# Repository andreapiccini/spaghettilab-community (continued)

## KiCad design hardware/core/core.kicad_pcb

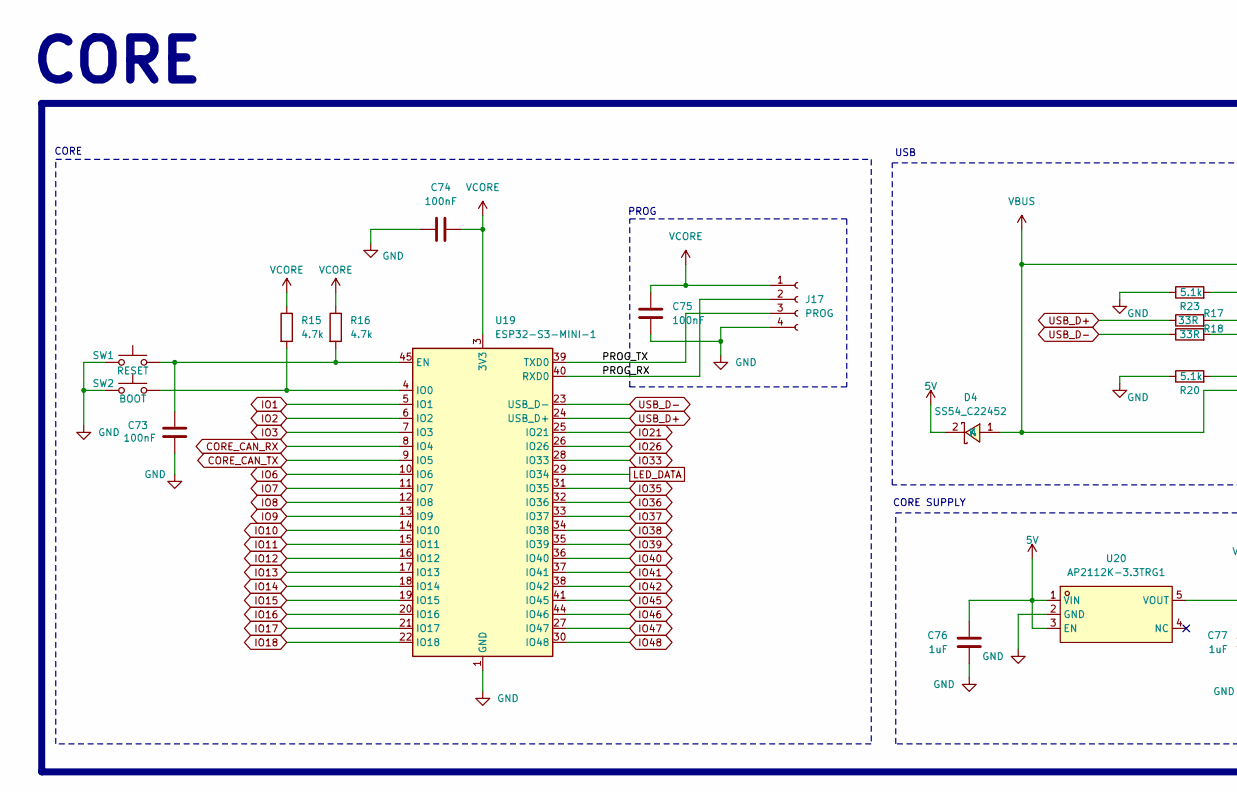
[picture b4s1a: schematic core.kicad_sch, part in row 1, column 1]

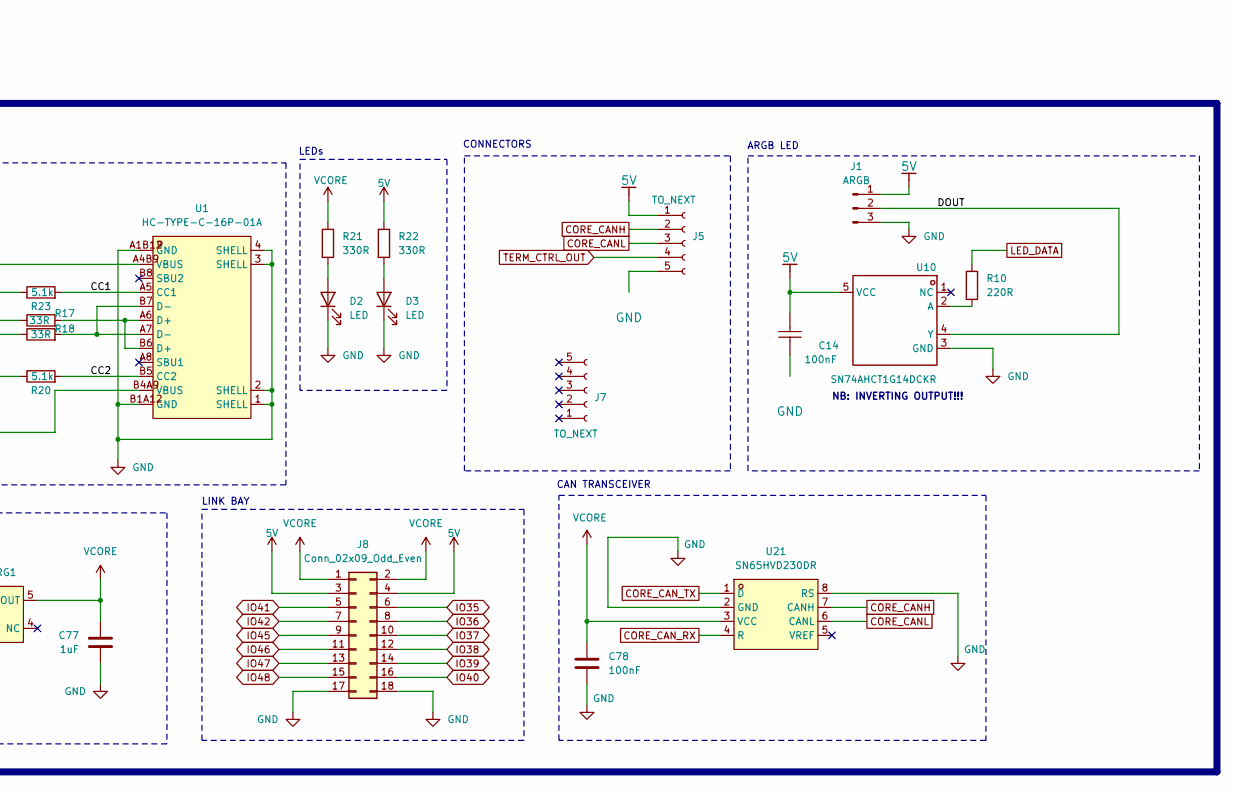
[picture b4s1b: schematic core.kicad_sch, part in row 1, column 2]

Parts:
C14, C73, C74, C75: 100nF; C0603; LCSC Part C1591
C76, C77: 1uF; C0603; LCSC Part C128624
C78: 100nF; C0603; MPN CL05B104KA5NNNC; LCSC Part C1591
D2, D3: LED; LED0603-RD; LCSC Part C19273150
D4: SS54_C22452; SMA_L4.4-W2.8-LS5.4-R-RD; MPN SS54; LCSC Part C22452
J1: ARGB; PinHeader_1x03_P2.54mm_Vertical
J5, J7: TO_NEXT; PinSocket_1x05_P2.54mm_Horizontal
J8: Conn_02x09_Odd_Even; PinSocket_2x09_P2.54mm_Horizontal
J17: PROG; PinSocket_1x04_P2.54mm_Vertical
R10: 220R; R0603; LCSC Part C22962
R15, R16: 4.7k; R0603; LCSC Part C99782
R17, R18: 33R; R0603; LCSC Part C2909394
R20, R23: 5.1k; R0603; LCSC Part C2907044
R21, R22: 330R; R0603; LCSC Part C105881
SW1: RESET; SW-SMD_4P-L5.1-W5.1-P3.70-LS6.5-TL_H1.5; LCSC Part C318884
SW2: BOOT; SW-SMD_4P-L5.1-W5.1-P3.70-LS6.5-TL_H1.5; LCSC Part C318884
U1: HC-TYPE-C-16P-01A; USB-C-SMD_HC-TYPE-C-16P-01A; MPN HC-TYPE-C-16P-01A; LCSC Part C2894897
U10: SN74AHCT1G14DCKR; SOT-353_L2.2-W1.4-P0.65-LS2.4-BR; Manufacturer Part SN74AHCT1G14DCKR; LCSC Part Name 单路施密特触发反相器
U19: ESP32-S3-MINI-1; ESP32-S2-MINI-1; LCSC Part C2913206
U20: AP2112K-3.3TRG1; SOT-25-5_L2.9-W1.6-P0.95-LS2.8-BL; MPN AP2112K-3.3TRG1; LCSC Part C51118
U21: SN65HVD230DR; SOIC-8_L4.9-W3.9-P1.27-LS6.0-BL; MPN SN65HVD230DR; LCSC Part C12084

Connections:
5V: C14.2, C76.2, D4.2 (K), J1.1, J5.1, J8.3, J8.4, R22.1, U10.5 (VCC), U20.1 (VIN), U20.3 (EN)
/CC1: R23.2, U1.A5 (CC1)
/CC2: R20.2, U1.B5 (CC2)
/DOUT: J1.2, U10.4 (Y)
/PROG_RX: J17.2, U19.40 (RXD0)
/PROG_TX: J17.3, U19.39 (TXD0)
CORE_CANH: J5.2, U21.7 (CANH)
CORE_CANL: J5.3, U21.6 (CANL)
CORE_CAN_RX: U19.8 (IO4), U21.4 (R)
CORE_CAN_TX: U19.9 (IO5), U21.1 (D)
GND: C14.1, C73.2, C74.1, C75.1, C76.1, C77.1, C78.2, D2.1 (K), D3.1 (K), J1.3, J5.5, J8.17, J8.18, J17.4, R20.1, R23.1, SW1.1, SW2.1, U1.1 (SHELL), U1.2 (SHELL), U1.3 (SHELL), U1.4 (SHELL), U1.A1B12 (GND), U1.B1A12 (GND), U10.3 (GND), U19.1 (GND), U19.2 (GND), U19.42 (GND), U19.43 (GND), U19.46 (GND), U19.47 (GND), U19.48 (GND), U19.49 (GND), U19.50 (GND), U19.51 (GND), U19.52 (GND), U19.53 (GND), U19.54 (GND), U19.55 (GND), U19.56 (GND), U19.57 (GND), U19.58 (GND), U19.59 (GND), U19.60 (GND), U19.61 (GND), U19.62 (GND), U19.63 (GND), U19.64 (GND), U19.65 (GND), U20.2 (GND), U21.2 (GND), U21.8 (RS); also elsewhere on the board
IO1: U19.5 (IO1)
IO2: U19.6 (IO2)
IO3: U19.7 (IO3)
IO6: U19.10 (IO6)
IO7: U19.11 (IO7)
IO8: U19.12 (IO8)
IO9: U19.13 (IO9)
IO10: U19.14 (IO10)
IO11: U19.15 (IO11)
IO12: U19.16 (IO12)
IO13: U19.17 (IO13)
IO14: U19.18 (IO14)
IO15: U19.19 (IO15)
IO16: U19.20 (IO16)
IO17: U19.21 (IO17)
IO18: U19.22 (IO18)
IO21: U19.25 (IO21)
IO26: U19.26 (IO26)
IO33: U19.28 (IO33)
IO35: J8.6, U19.31 (IO35)
IO36: J8.8, U19.32 (IO36)
IO37: J8.10, U19.33 (IO37)
IO38: J8.12, U19.34 (IO38)
IO39: J8.14, U19.35 (IO39)
IO40: J8.16, U19.36 (IO40)
IO41: J8.5, U19.37 (IO41)
IO42: J8.7, U19.38 (IO42)
IO45: J8.9, U19.41 (IO45)
IO46: J8.11, U19.44 (IO46)
IO47: J8.13, U19.27 (IO47)
IO48: J8.15, U19.30 (IO48)
LED_DATA: R10.1, U19.29 (IO34)
unnamed: D2.2 (A), R21.2
unnamed: D3.2 (A), R22.2
unnamed: R17.2, U1.A6 (D+), U1.B6 (D+)
unnamed: R18.2, U1.A7 (D-), U1.B7 (D-)
unnamed: R10.2, U10.2 (A)
unnamed: C73.1, R16.2, SW1.3, U19.45 (EN)
unnamed: R15.2, SW2.3, U19.4 (IO0)
TERM_CTRL_OUT: J5.4
USB_D+: R17.1, U19.24 (USB_D+)
USB_D-: R18.1, U19.23 (USB_D-)
VBUS: D4.1 (A), U1.A4B9 (VBUS), U1.B4A9 (VBUS)
VCORE: C74.2, C75.2, C77.2, C78.1, J8.1, J8.2, J17.1, R15.1, R16.1, R21.1, U19.3 (3V3), U20.5 (VOUT), U21.3 (VCC)

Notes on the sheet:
CAN TRANSCEIVER
CORE SUPPLY
CORE
LINK BAY
USB
LEDs
NB: INVERTING OUTPUT!!!
PROG
CONNECTORS
ARGB LED

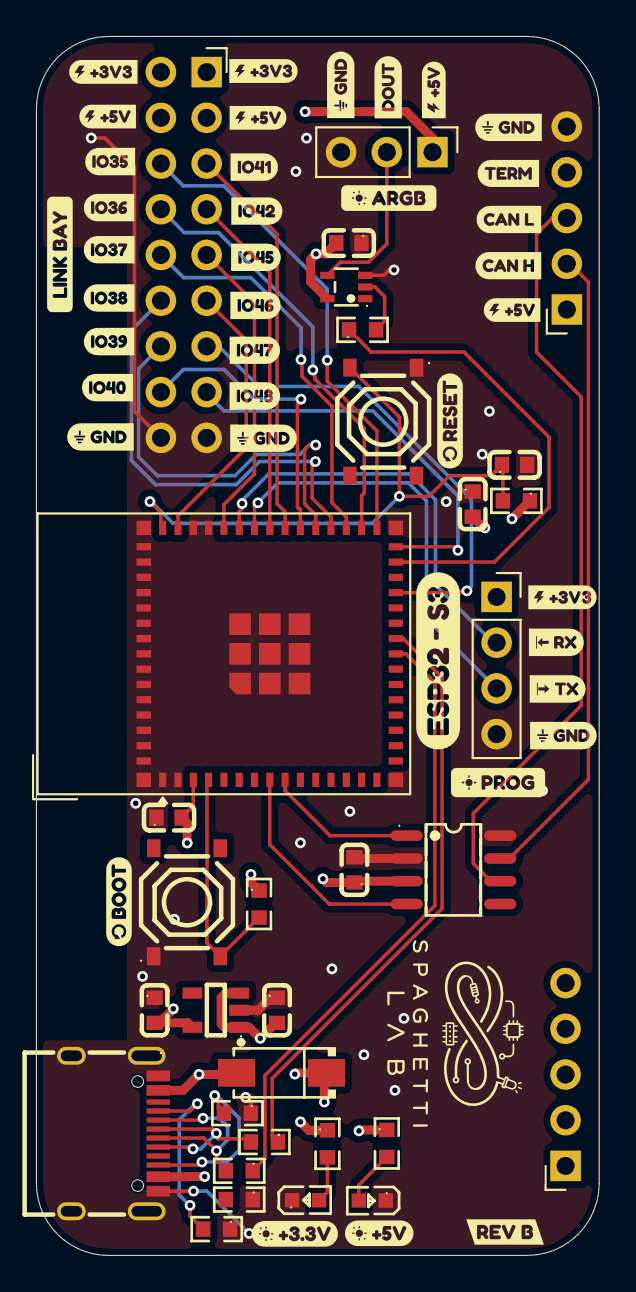
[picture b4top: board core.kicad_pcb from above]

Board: 4 copper layers, 31.3 x 67.7 mm, 71 parts (0 on the bottom side), 35 nets.

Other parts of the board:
R19: 5.1k; R0603
kobee-studio-6AA83E37, kobee-studio-6AA91FA3, kobee-studio-6AA91FB4, kobee-studio-6AA91FC0, kobee-studio-6AA91FC9, kobee-studio-6AA91FD2, kobee-studio-6AA924CD, kobee-studio-6AA9201C, kobee-studio-6AA9246B, kobee-studio-6AA9247D, kobee-studio-6AA9248F, kobee-studio-6AA9311E, kobee-studio-6AA9313B, kobee-studio-6AA9314C, kobee-studio-6AA9337A, kobee-studio-6AA91364, kobee-studio-6AA92015, kobee-studio-6AA92023, kobee-studio-6AA92029, kobee-studio-6AA92049, kobee-studio-6AA92476, kobee-studio-6AA92486, kobee-studio-6AA93134, kobee-studio-6AA93141, kobee-studio-6AA93147, kobee-studio-6AA93221, kobee-studio-6AABEAAD, kobee-studio-6AABEB0E, kobee-studio-6AABEB1D, kobee-studio-6AABEB02, kobee-studio-6AABEB2F, kobee-studio-6AABEB3C, kobee-studio-6AABEB18, kobee-studio-6AACD9C8, kobee-studio-6AACD9D1, kobee-studio-6AACD93B, kobee-studio-6AACD935, kobee-studio-6AACD940: Kobee Studio; kobee-studio-6AA83D3C
kobee-studio-6AA93394: Kobee Studio; kobee-studio-6AA91E6F

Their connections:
GND: R19.1; also elsewhere on the board

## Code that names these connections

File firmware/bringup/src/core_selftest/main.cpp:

#include <Arduino.h>
#include <WiFi.h>
#include <BLEDevice.h>
#include <BLEServer.h>
#include <esp_chip_info.h>
#include <esp_flash.h>
#include <esp_mac.h>

#include "sk6812_rmt.h"

// Pin map from hardware/core/core.kicad_sch + core.kicad_pcb (U19 ESP32-S3-MINI-1).
// USB_D+/D- = GPIO20/19 (native CDC). LED_DATA = GPIO34 via SN74AHCT1G14 (invert!).
// CAN: GPIO5 = CORE_CAN_TX -> SN65HVD230 D, GPIO4 = CORE_CAN_RX <- R (local echo).
// SW2 BOOT = GPIO0. PROG J17 = GPIO43 TX / GPIO44 RX. Link Bay J8 = GPIO35..42,45..48.

static const int kLedGpio = 34;
static const int kCanRx = 4;
static const int kCanTx = 5;
static const int kBoot = 0;
static const int kBayGpios[] = {35, 36, 37, 38, 39, 40, 41, 42, 45, 46, 47, 48};

static bool s_ble_ok = false;

static void banner() {
    Serial.println();
    Serial.println("================================================");
    Serial.println("  SpaghettiLAB CORE  ESP32-S3 self-test");
    Serial.println("  Schematic: hardware/core/core.kicad_sch");
    Serial.println("================================================");
    Serial.println("Commands:  a=all  r=rgb  c=can  w=wifi  b=ble  g=gpio  h=help");
}

static void test_chip() {
    Serial.println();
    Serial.println("[1] Chip / flash / USB");
    Serial.printf("    model     %s  rev %d  cores %d\n", ESP.getChipModel(), ESP.getChipRevision(), ESP.getChipCores());
    Serial.printf("    CPU       %u MHz\n", ESP.getCpuFreqMHz());
    Serial.printf("    flash     %u KB\n", ESP.getFlashChipSize() / 1024);
    Serial.printf("    PSRAM     %u KB\n", ESP.getPsramSize() / 1024);
    Serial.printf("    heap      %u free / %u min\n", ESP.getFreeHeap(), ESP.getMinFreeHeap());
    uint8_t mac[6] = {};
    esp_read_mac(mac, ESP_MAC_WIFI_STA);
    Serial.printf("    Wi-Fi MAC %02X:%02X:%02X:%02X:%02X:%02X\n", mac[0], mac[1], mac[2], mac[3], mac[4], mac[5]);
    Serial.println("    USB CDC   PASS  (you are reading this)");
}

static void test_rgb() {
    Serial.println();
    Serial.println("[2] SK6812 on GPIO34 (inverter U10 — look at the CORE LED)");
    const uint8_t colors[][3] = {{48, 0, 0}, {0, 48, 0}, {0, 0, 48}, {48, 48, 48}, {0, 0, 0}};
    const char *names[] = {"RED", "GREEN", "BLUE", "WHITE", "OFF"};
    for (int i = 0; i < 5; ++i) {
        sk6812_fill(colors[i][0], colors[i][1], colors[i][2]);
        sk6812_show();
        Serial.printf("    %s\n", names[i]);
        delay(400);
    }
    Serial.println("    PASS if the on-board ARGB stepped through those colors");
}

static void test_boot() {
    pinMode(kBoot, INPUT_PULLUP);
    const int level = digitalRead(kBoot);
    Serial.println();
    Serial.println("[3] BOOT SW2 on GPIO0");
    Serial.printf("    GPIO0 = %s  (released = HIGH, held = LOW)\n", level ? "HIGH" : "LOW");
}

static void test_can_echo() {
    Serial.println();
    Serial.println("[4] CAN PHY echo  GPIO5 TX -> SN65HVD230 -> GPIO4 RX");
    gpio_reset_pin((gpio_num_t)kCanTx);
    gpio_reset_pin((gpio_num_t)kCanRx);
    pinMode(kCanTx, OUTPUT);
    pinMode(kCanRx, INPUT);
    digitalWrite(kCanTx, HIGH);
    delay(5);
    const int rec = digitalRead(kCanRx);
    digitalWrite(kCanTx, LOW);
    delay(5);
    const int dom = digitalRead(kCanRx);
    digitalWrite(kCanTx, HIGH);
    delay(5);
    const int rec2 = digitalRead(kCanRx);
    const bool ok = rec == HIGH && rec2 == HIGH;
    Serial.printf("    TX recessive HIGH -> RX=%s\n", rec ? "HIGH" : "LOW");
    Serial.printf("    TX dominant  LOW  -> RX=%s  (local echo often stays HIGH if bus is open)\n",
                  dom ? "HIGH" : "LOW");
    Serial.printf("    TX recessive HIGH -> RX=%s\n", rec2 ? "HIGH" : "LOW");
    if (ok) {
        Serial.println("    PASS  transceiver is driving RX (idle/recessive seen)");
    } else {
        Serial.println("    FAIL  GPIO4 did not follow recessive HIGH — check U21 / 3V3 / CAN wiring");
    }
    if (dom == LOW) {
        Serial.println("    note: dominant echoed — bus or terminator is loading the pair");
    }
}

static void test_wifi() {
    Serial.println();
    Serial.println("[5] Wi-Fi scan");
    WiFi.mode(WIFI_STA);
    WiFi.disconnect(true, true);
    delay(80);
    const int n = WiFi.scanNetworks(/*async=*/false, /*hidden=*/true);
    if (n < 0) {
        Serial.println("    FAIL  scan error");
        return;
    }
    Serial.printf("    found %d AP(s)\n", n);
    for (int i = 0; i < n && i < 8; ++i) {
        Serial.printf("      %s  ch %d  %d dBm\n", WiFi.SSID(i).c_str(), WiFi.channel(i), WiFi.RSSI(i));
    }
    Serial.println(n > 0 ? "    PASS" : "    WARN  no APs (radio may still be OK)");
    WiFi.scanDelete();
    WiFi.mode(WIFI_OFF);
}

static void test_ble() {
    Serial.println();
    Serial.println("[6] BLE advertise  'SL-CORE-TEST'");
    if (!s_ble_ok) {
        BLEDevice::init("SL-CORE-TEST");
        BLEServer *server = BLEDevice::createServer();
        (void)server;
        BLEAdvertising *adv = BLEDevice::getAdvertising();
        adv->setScanResponse(true);
        adv->start();
        s_ble_ok = true;
    }
    Serial.println("    PASS  advertising (scan with a phone)");
}

static void test_bay_gpio() {
    Serial.println();
    Serial.println("[7] Link Bay J8 GPIOs (INPUT_PULLUP)");
    for (int gpio : kBayGpios) {
        pinMode(gpio, INPUT_PULLUP);
        delayMicroseconds(50);
        const int v = digitalRead(gpio);
        Serial.printf("    GPIO%02d  %s\n", gpio, v ? "HIGH" : "LOW ");
    }
    Serial.println("    floating pins should read HIGH; a short to GND reads LOW");
}

static void run_all() {
    test_chip();
    test_rgb();
    test_boot();
    test_can_echo();
    test_wifi();
    test_ble();
    test_bay_gpio();
    Serial.println();
    Serial.println("Done. RGB returns to slow cycle. Type h for commands.");
}

void setup() {
    Serial.begin(115200);
    delay(400);
    sk6812_begin(kLedGpio, 1, /*invert_out=*/true);
    sk6812_fill(0, 0, 24);
    sk6812_show();
    banner();
    run_all();
}

void loop() {
    while (Serial.available()) {
        const int c = Serial.read();
        if (c == 'a' || c == 'A') run_all();
        else if (c == 'r' || c == 'R') test_rgb();
        else if (c == 'c' || c == 'C') test_can_echo();
        else if (c == 'w' || c == 'W') test_wifi();
        else if (c == 'b' || c == 'B') test_ble();
        else if (c == 'g' || c == 'G') test_bay_gpio();
        else if (c == 'h' || c == 'H' || c == '?') banner();
    }

    static uint32_t last = 0;
    const uint32_t now = millis();
    if (now - last >= 800) {
        last = now;
        const uint8_t phase = (now / 800) % 3;
        if (phase == 0) sk6812_fill(32, 0, 0);
        else if (phase == 1) sk6812_fill(0, 32, 0);
        else sk6812_fill(0, 0, 32);
        sk6812_show();
    }
}

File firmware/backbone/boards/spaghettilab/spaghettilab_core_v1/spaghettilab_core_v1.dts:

/dts-v1/;

#include <espressif/esp32c3/esp32c3_mini_n4.dtsi>
#include <espressif/partitions_0x0_default.dtsi>
#include <zephyr/dt-bindings/pinctrl/esp-pinctrl-common.h>
#include <zephyr/dt-bindings/pinctrl/esp32c3-pinctrl.h>
#include <zephyr/dt-bindings/pinctrl/esp32c3-gpio-sigmap.h>

/ {
	model = "Spaghetti LAB Core V1";
	compatible = "spaghettilab,core-v1", "espressif,esp32c3";

	chosen {
		zephyr,sram = &sram1;
		zephyr,console = &usb_serial;
		zephyr,shell-uart = &usb_serial;
		zephyr,flash = &flash0;
		zephyr,code-partition = &slot0_partition;
		zephyr,uart-mcumgr = &uart1;
		zephyr,bt-hci = &esp32_bt_hci;
	};

	aliases {
		i2c-0 = &i2c0;
	};

	spaghetti_ports {
		compatible = "simple-bus";
		#address-cells = <1>;
		#size-cells = <0>;

		port0: port@0 {
			compatible = "spaghettilab,port";
			reg = <0>;
			i2c = <&i2c0>;
			status = "okay";
		};

		/*
		 * A second connector exposing five raw digital signal lines on
		 * ESP32-C3 SuperMini breakout pins 0, 1, 5, 6, 7 — every
		 * production pin reference here is the SuperMini's own labeled
		 * breakout pin, chosen deliberately excluding the pins already
		 * wired above (GPIO3/GPIO4, I2C0) and GPIO2/GPIO8/GPIO9 (ESP32-C3
		 * strapping pins, sampled by the boot ROM at reset to select
		 * flash voltage/download mode — safe to use as GPIO once running,
		 * but risky to wire to anything that could hold them low across a
		 * reset). Each line is both an input-gpios and output-gpios entry
		 * at the same signal index: the physical pin is bidirectional,
		 * which direction is actually used is a Module driver's own
		 * choice (its declared required_capabilities), not fixed here.
		 */
		port1: port@1 {
			compatible = "spaghettilab,port";
			reg = <1>;
			input-gpios = <&gpio0 0 GPIO_ACTIVE_HIGH>,
				      <&gpio0 1 GPIO_ACTIVE_HIGH>,
				      <&gpio0 5 GPIO_ACTIVE_HIGH>,
				      <&gpio0 6 GPIO_ACTIVE_HIGH>,
				      <&gpio0 7 GPIO_ACTIVE_HIGH>;
			output-gpios = <&gpio0 0 GPIO_ACTIVE_HIGH>,
				       <&gpio0 1 GPIO_ACTIVE_HIGH>,
				       <&gpio0 5 GPIO_ACTIVE_HIGH>,
				       <&gpio0 6 GPIO_ACTIVE_HIGH>,
				       <&gpio0 7 GPIO_ACTIVE_HIGH>;
			status = "okay";
		};
	};

	spaghetti_flows {
		compatible = "simple-bus";
		#address-cells = <1>;
		#size-cells = <0>;

		flow0: flow@0 {
			compatible = "spaghettilab,flow";
			reg = <0>;
			port = <&port0>;
			direction = "field-to-core";
			signal-count = <5>;
			function-bay-count = <0>;
			status = "okay";
		};

		flow1: flow@1 {
			compatible = "spaghettilab,flow";
			reg = <1>;
			port = <&port1>;
			direction = "bidirectional";
			signal-count = <5>;
			function-bay-count = <0>;
			status = "okay";
		};
	};

	maintenance_link0: maintenance-link {
		compatible = "spaghettilab,maintenance-link";
		normal-bus = <&i2c0>;
		maintenance-uart = <&uart1>;
		bootstrap-window-ms = <500>;
		status = "okay";
	};
};

&pinctrl {
	spaghetti_i2c0_default: spaghetti_i2c0_default {
		group1 {
			pinmux = <I2C0_SDA_GPIO3>, <I2C0_SCL_GPIO4>;
			bias-pull-up;
			drive-open-drain;
			output-high;
		};
	};

	spaghetti_uart1_maintenance: spaghetti_uart1_maintenance {
		group1 {
			pinmux = <UART1_RX_GPIO3>, <UART1_TX_GPIO4>;
		};
	};

	spaghetti_uart1_probe: spaghetti_uart1_probe {
		group1 {
			pinmux = <UART1_RX_GPIO3>;
			bias-pull-up;
		};
	};
};

&usb_serial {
	status = "okay";
};

&i2c0 {
	status = "okay";
	clock-frequency = <I2C_BITRATE_STANDARD>;
	pinctrl-0 = <&spaghetti_i2c0_default>;
	pinctrl-names = "default";
};

&uart1 {
	status = "okay";
	current-speed = <115200>;
	pinctrl-0 = <&spaghetti_uart1_probe>;
	pinctrl-1 = <&spaghetti_uart1_maintenance>;
	pinctrl-names = "default", "sleep";
};

&gpio0 {
	status = "okay";
};

&trng0 {
	status = "okay";
};

&wifi {
	status = "okay";
};

&esp32_bt_hci {
	status = "okay";
};
